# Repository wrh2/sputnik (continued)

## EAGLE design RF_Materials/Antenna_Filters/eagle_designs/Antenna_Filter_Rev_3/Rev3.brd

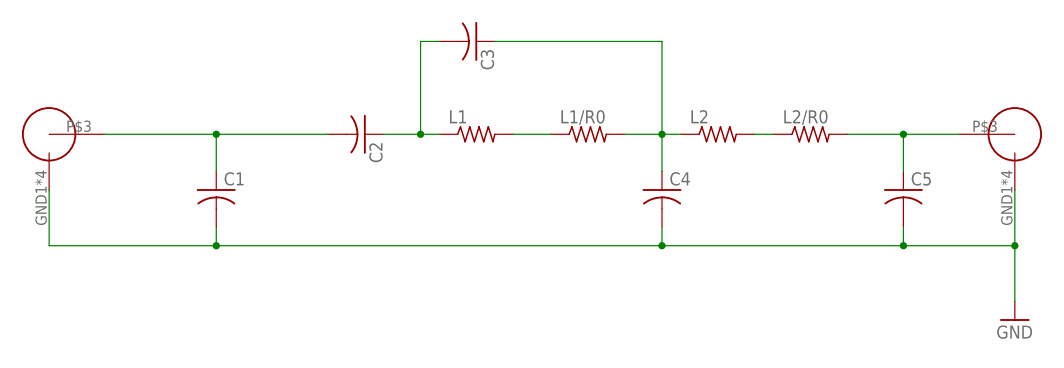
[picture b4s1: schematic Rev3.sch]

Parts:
C1, C2, C3, C4, C5: C-USC0603; C0603
L1, L1/R0, L2, L2/R0: R-US_R0603; R0603
U$1, U$2: SMAJ716-ND

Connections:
C3: C3.1, C4.1, L1/R0.2, L2.1
GND: C1.2, C4.2, C5.2, U$1.GND1 (OUTERCONDUCTOR), U$1.GND2 (OUTERCONDUCTOR), U$1.GND3 (OUTERCONDUCTOR), U$1.GND4 (OUTERCONDUCTOR), U$2.GND1 (OUTERCONDUCTOR), U$2.GND2 (OUTERCONDUCTOR), U$2.GND3 (OUTERCONDUCTOR), U$2.GND4 (OUTERCONDUCTOR)
unnamed: C5.1, L2/R0.2, U$2.P$3 (CENTERCONDUCTOR)
unnamed: L2.2, L2/R0.1
unnamed: C2.1, C3.2, L1.1
unnamed: L1.2, L1/R0.1
unnamed: C1.1, C2.2, U$1.P$3 (CENTERCONDUCTOR)

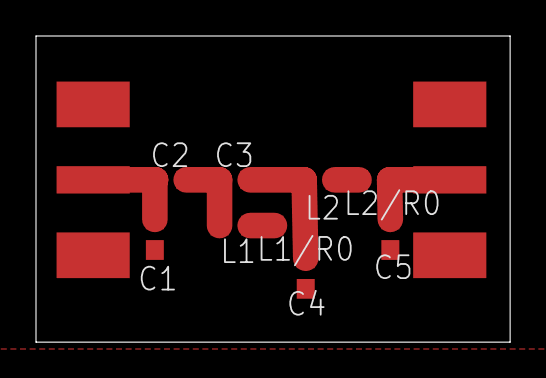
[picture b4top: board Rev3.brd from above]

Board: 2 copper layers, 26.3 x 17.0 mm, 11 parts (0 on the bottom side), 7 nets.

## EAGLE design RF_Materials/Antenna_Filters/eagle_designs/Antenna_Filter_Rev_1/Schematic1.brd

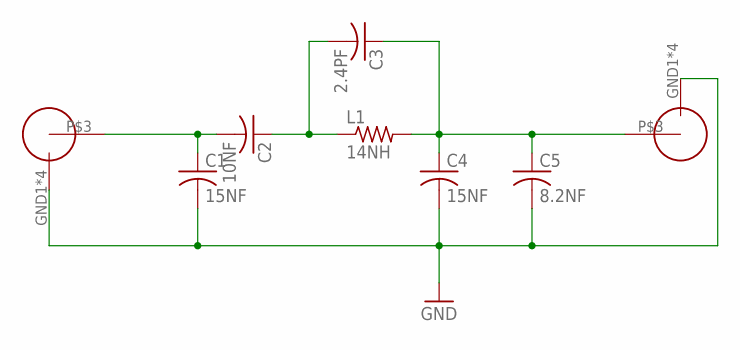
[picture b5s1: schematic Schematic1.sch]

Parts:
C1, C4: 15NF; C0603
C2: 10NF; C0603
C3: 2.4PF; C0603
C5: 8.2NF; C0603
GND: SMAJ716-ND
L1: 14NH; R0603
U$2: SMAJ716-ND

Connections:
GND: C1.2, C4.2, C5.2, GND.GND1 (OUTERCONDUCTOR), GND.GND2 (OUTERCONDUCTOR), GND.GND3 (OUTERCONDUCTOR), GND.GND4 (OUTERCONDUCTOR), U$2.GND1 (OUTERCONDUCTOR), U$2.GND2 (OUTERCONDUCTOR), U$2.GND3 (OUTERCONDUCTOR), U$2.GND4 (OUTERCONDUCTOR)
unnamed: C3.1, C4.1, C5.1, L1.2, U$2.P$3 (CENTERCONDUCTOR)
unnamed: C2.1, C3.2, L1.1
unnamed: C1.1, C2.2, GND.P$3 (CENTERCONDUCTOR)

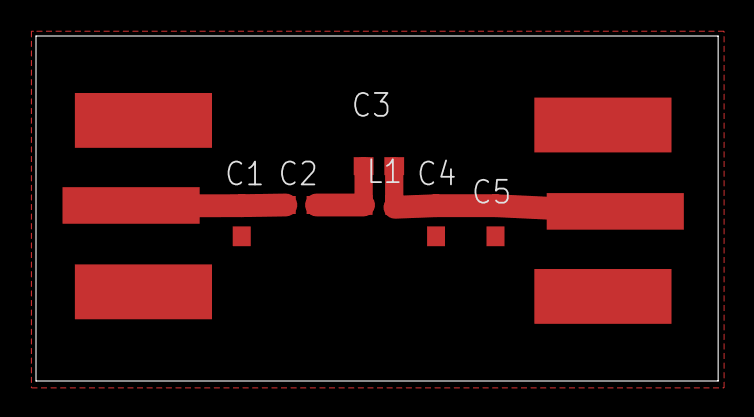
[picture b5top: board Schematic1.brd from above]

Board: 2 copper layers, 37.9 x 19.2 mm, 8 parts (0 on the bottom side), 4 nets.

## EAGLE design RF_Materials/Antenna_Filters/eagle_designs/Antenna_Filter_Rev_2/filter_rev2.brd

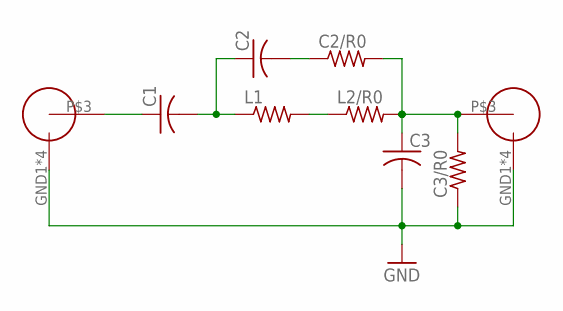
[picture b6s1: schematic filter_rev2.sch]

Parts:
C1, C2, C3: C-USC0603; C0603
C2/R0, C3/R0: R-US_R0603; R0603
L1, L2/R0: R-US_R0603; R0603
U$1, U$2: SMAJ716-ND

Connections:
GND: C3.2, C3/R0.1, U$1.GND1 (OUTERCONDUCTOR), U$1.GND2 (OUTERCONDUCTOR), U$1.GND3 (OUTERCONDUCTOR), U$1.GND4 (OUTERCONDUCTOR), U$2.GND1 (OUTERCONDUCTOR), U$2.GND2 (OUTERCONDUCTOR), U$2.GND3 (OUTERCONDUCTOR), U$2.GND4 (OUTERCONDUCTOR)
unnamed: C1.1, U$1.P$3 (CENTERCONDUCTOR)
unnamed: C2.2, C2/R0.1
unnamed: C1.2, C2.1, L1.1
unnamed: C2/R0.2, C3.1, C3/R0.2, L2/R0.2, U$2.P$3 (CENTERCONDUCTOR)
unnamed: L1.2, L2/R0.1

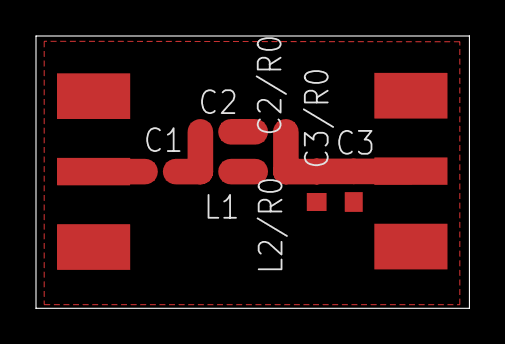
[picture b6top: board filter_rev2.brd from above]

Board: 2 copper layers, 24.1 x 15.1 mm, 9 parts (0 on the bottom side), 6 nets.

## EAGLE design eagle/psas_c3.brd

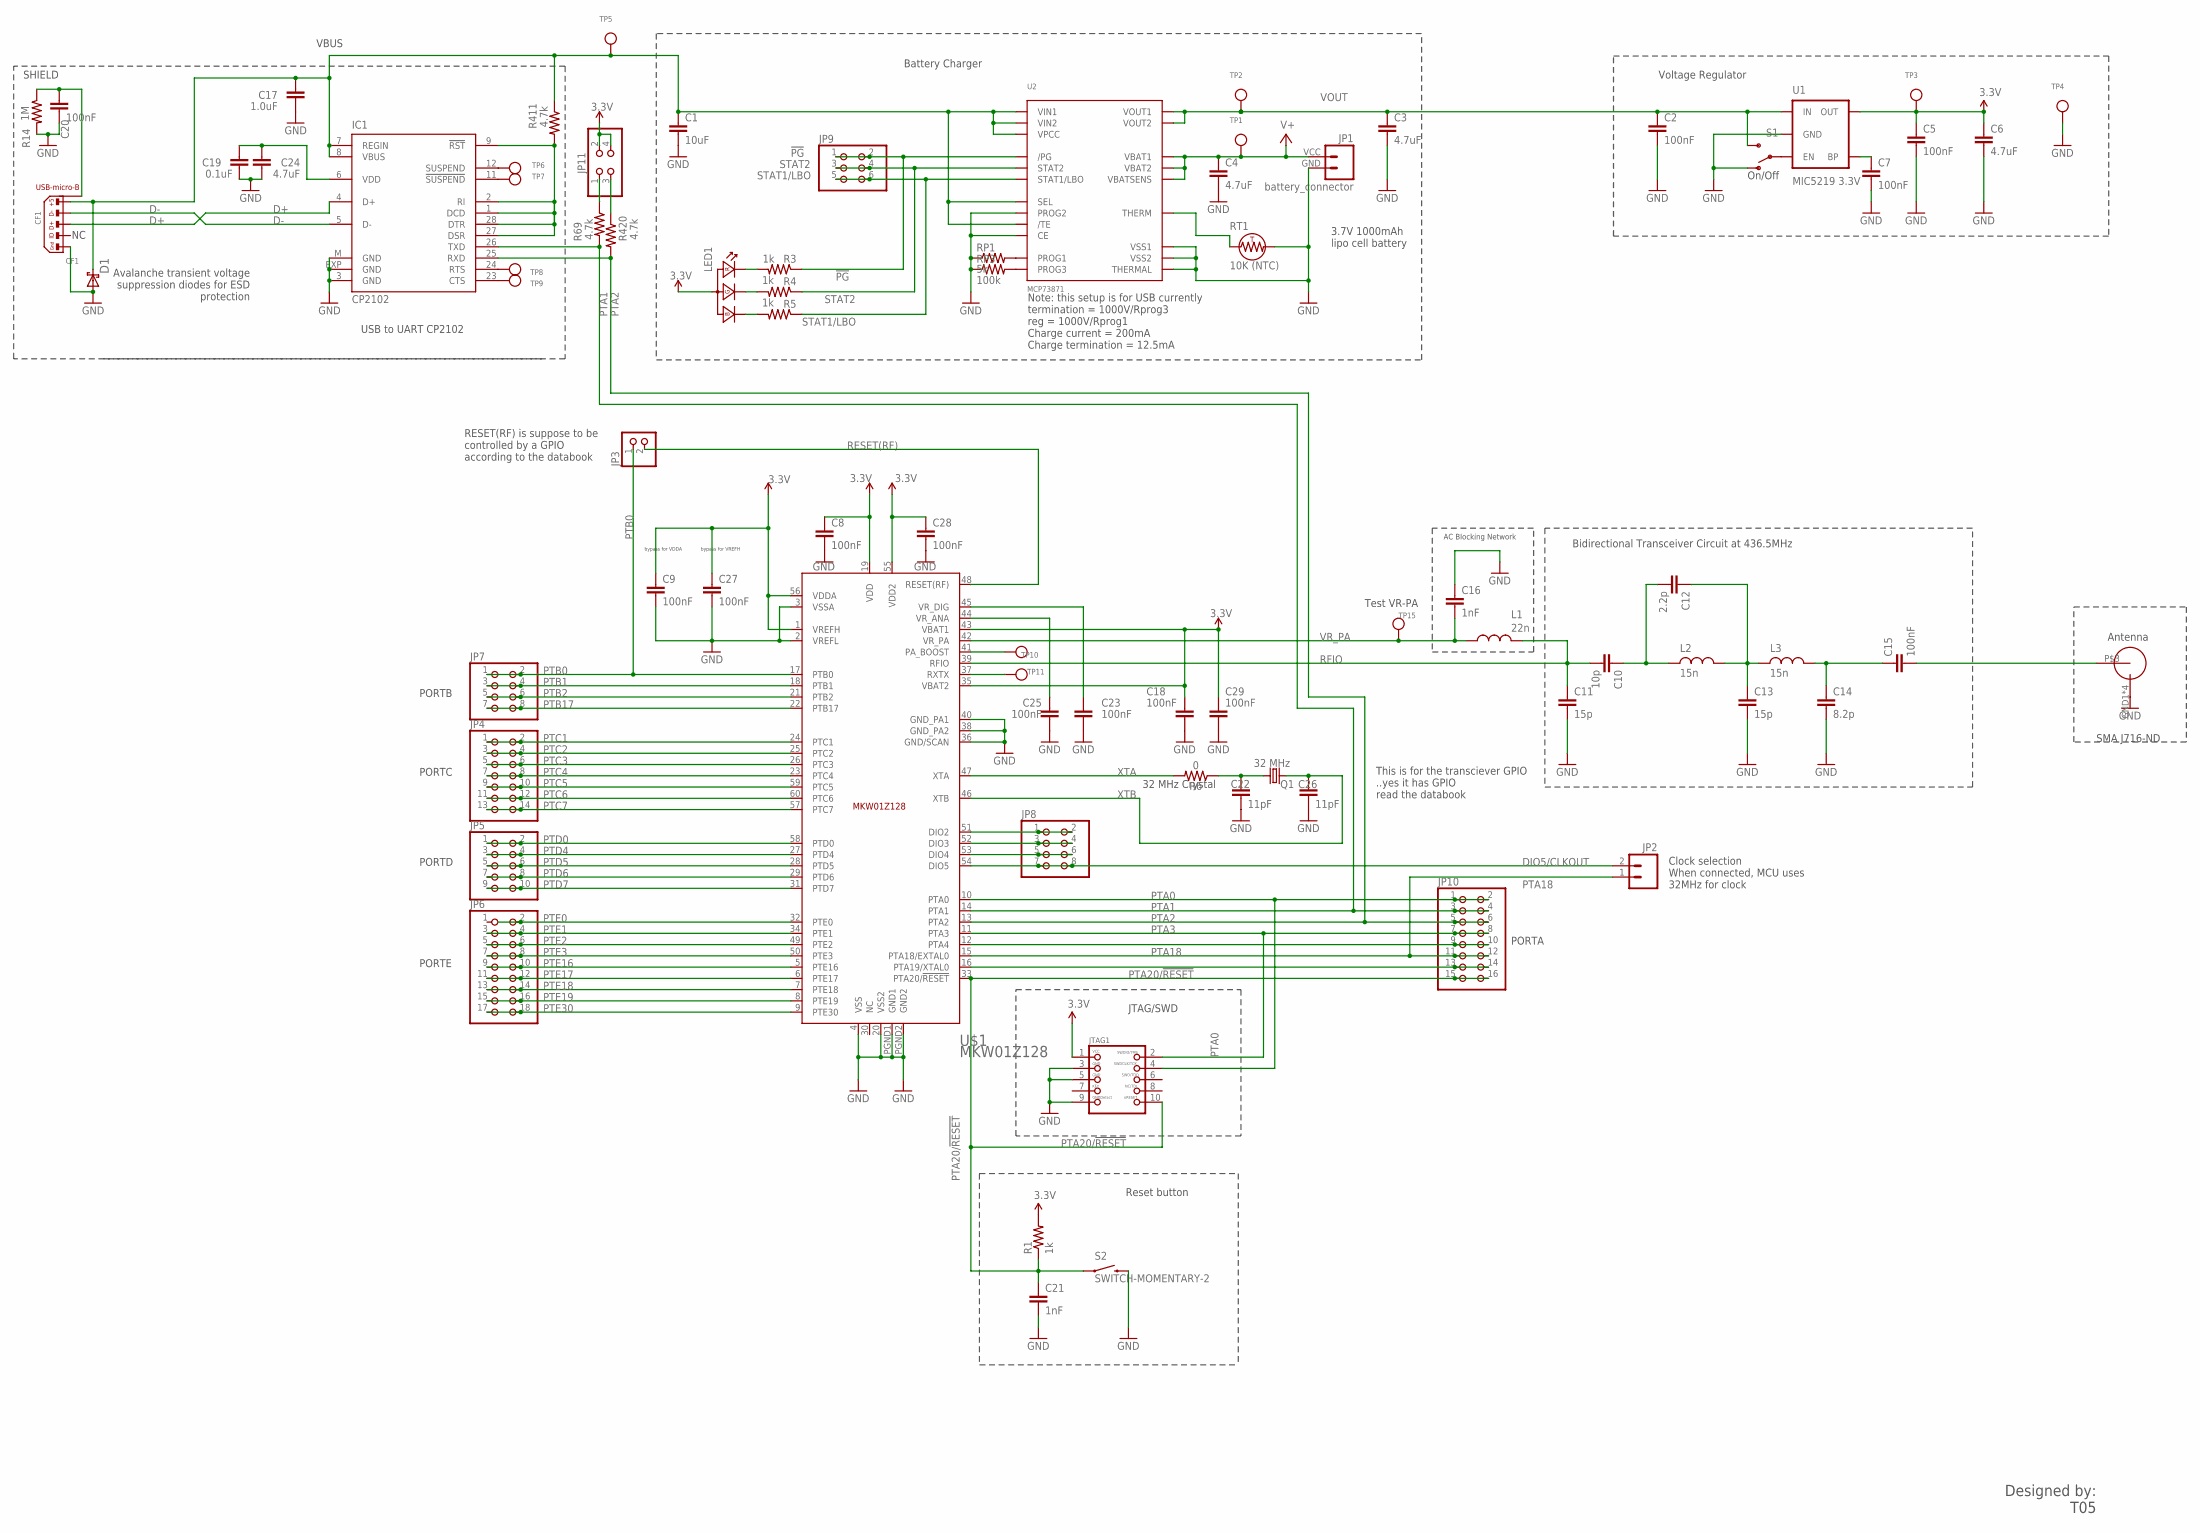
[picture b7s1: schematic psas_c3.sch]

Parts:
C1: 10uF; .0603-B-NOSILK
C2, C5, C7, C15, C20: 100nF; .0603-B-NOSILK
C3, C4, C6, C24: 4.7uF; .0603-B-NOSILK
C8, C9, C18, C23, C25, C27, C28, C29: 100nF; .0603-B-NOSILK; MPN GRM188R71C104KA01D
C10: 10p; .0603-B-NOSILK
C11, C13: 15p; .0603-B-NOSILK
C12: 2.2p; .0603-B-NOSILK
C14: 8.2p; .0603-B-NOSILK
C16, C21: 1nF; .0603-B-NOSILK
C17: 1.0uF; .0603-B-NOSILK
C19: 0.1uF; .0603-B-NOSILK
C22, C26: 11pF; .0603-B-NOSILK; MPN GRM188R71C104KA01D
CF1: CF1; USB-MICRO-B-PTH-HIROSE
D1: DIODE_SCHOTTKY_1N5819; SOD-123
IC1: CP2102; MLP28
JP1: battery_connector; SPARKFUN-CONNECTORS_JST-2-SMD-VERT
JP2: M02PTH; 1X02
JP3: PINHD-1X2; 1X02
JP4: PINHD-2X7; 2X07
JP5: PINHD-2X5; 2X05
JP6: PINHD-2X9; 2X09
JP7, JP8: PINHD-2X4; 2X04
JP9: PINHD-2X3; 2X03
JP10: PINHD-2X8; 2X08
JP11: PINHD-2X2; 2X02
JTAG1: JTAG-CORTEXM3MOLEX; CORTEXM3_SWD10_MOLEX
L1: 22n; .0603-B-NOSILK
L2, L3: 15n; .0603-B-NOSILK
LED1: LED_RGB_COMMON_ANODE-1.6X1.26; KINGBRITE_RGBLED_1.6X1.26
Q1: 32 MHz; FC-12M
R1, R3, R4, R5: 1k; .0603-B-NOSILK
R6: 0; .0603-B-NOSILK
R14: 1M; .0603-B-NOSILK
R69, R411, R420: 4.7k; .0603-B-NOSILK
RP1: 5k; .0603-B-NOSILK
RP3: 100k; .0603-B-NOSILK
RT1: 10K (NTC); R1206
S1: SWITCH-SPSTPTH; SWITCH-SPDT
S2: SWITCH-MOMENTARY-2; TACTILE_SWITCH_TALL
TP1, TP2, TP3, TP4, TP5, TP6, TP7, TP8, TP9, TP10, TP11, TP15: TESTPOINTROUND0.5MM; TESTPOINT_ROUND_0.5MM
U1: MIC5219 3.3V; SPARKFUN-POWERIC_SOT23-5
U2: MCP73871; QFN20_4MM
U$1: MKW01Z128; MPN MKW01Z128CHN
U$2: SMAJ716-ND

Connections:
3.3V: C5.1, C6.1, C8.1, C9.1, C18.1, C27.1, C28.1, C29.1, JP11.2, JP11.4, JTAG1.1, LED1.2 (COMMON_ANODE), R1.2, TP3.P$1, U1.5 (OUT), U$1.1 (VREFH), U$1.19 (VDD), U$1.35 (VBAT2), U$1.43 (VBAT1), U$1.55 (VDD2), U$1.56 (VDDA)
!PG: JP9.1, JP9.2, R3.1, U2.P$6 (/PG)
D+: CF1.3, IC1.4 (D+)
D-: CF1.2, IC1.5 (D-)
DIO5/CLKOUT: JP2.2, JP8.7, JP8.8, U$1.54 (DIO5)
GND: C1.2, C2.2, C3.2, C4.2, C5.2, C6.2, C7.2, C8.2, C9.2, C11.2, C13.2, C14.2, C16.1, C17.2, C18.2, C19.2, C20.2, C21.2, C22.2, C23.2, C24.2, C25.2, C26.2, C27.2, C28.2, C29.2, CF1.5, D1.ANODE, IC1.3 (GND), IC1.EXP (GND), IC1.M (GND), JP1.GND (1), JTAG1.3, JTAG1.5, JTAG1.9, R14.2, RP1.1, RP3.1, RT1.2, S1.1 (O), S2.B2 (2), TP4.P$1, U1.2 (GND), U2.P$4 (PROG2), U2.P$10 (VSS1), U2.P$11 (VSS2), U2.P$17 (CE), U2.P$21 (THERMAL), U$1.2 (VREFL), U$1.3 (VSSA), U$1.4 (VSS), U$1.20 (VSS2), U$1.36 (GND/SCAN), U$1.38 (GND_PA2), U$1.40 (GND_PA1), U$1.PGND1 (GND1), U$1.PGND2 (GND2), U$2.GND1 (OUTERCONDUCTOR), U$2.GND2 (OUTERCONDUCTOR), U$2.GND3 (OUTERCONDUCTOR), U$2.GND4 (OUTERCONDUCTOR)
unnamed: C7.1, U1.4 (BP)
unnamed: LED1.3 (RK), R3.2
unnamed: LED1.4 (GK), R4.2
unnamed: LED1.1 (BK), R5.2
unnamed: IC1.12 (SUSPEND), TP6.P$1
unnamed: RT1.1, U2.P$5 (THERM)
unnamed: IC1.11 (!SUSPEND), TP7.P$1
unnamed: S1.2, U1.3 (EN)
unnamed: RP1.2, U2.P$13 (PROG1)
unnamed: RP3.2, U2.P$12 (PROG3)
unnamed: IC1.24 (RTS), TP8.P$1
unnamed: C22.1, Q1.2, R6.1
unnamed: TP10.P$1, U$1.41 (PA_BOOST)
unnamed: C25.1, U$1.44 (VR_ANA)
unnamed: TP11.P$1, U$1.37 (RXTX)
unnamed: JP8.1, JP8.2, U$1.51 (DIO2)
unnamed: C12.1, C13.1, L2.2, L3.1
unnamed: C10.1, C12.2, L2.1
unnamed: C15.2, U$2.P$3 (CENTERCONDUCTOR)
unnamed: JP8.3, JP8.4, U$1.52 (DIO3)
unnamed: C14.1, C15.1, L3.2
unnamed: C23.1, U$1.45 (VR_DIG)
unnamed: JP8.5, JP8.6, U$1.53 (DIO4)
unnamed: C19.1, C24.1, IC1.6 (VDD)
unnamed: IC1.23 (CTS), TP9.P$1
unnamed: JP10.9, JP10.10, U$1.12 (PTA4)
unnamed: JP10.13, JP10.14, U$1.16 (PTA19/XTAL0)
unnamed: JP11.1, R69.1
unnamed: JP11.3, R420.1
unnamed: IC1.1 (DCD), IC1.2 (RI), IC1.9 (!RST), IC1.27 (DSR), IC1.28 (DTR), R411.2
unnamed: C20.1, CF1.S1 (SHIELD), CF1.S2 (SHIELD), CF1.S3 (SHIELD), CF1.S4 (SHIELD), R14.1
PTA0: JP10.1, JP10.2, JTAG1.4, U$1.10 (PTA0)
PTA1: IC1.26 (TXD), JP10.3, JP10.4, R69.2, U$1.14 (PTA1)
PTA2: IC1.25 (RXD), JP10.5, JP10.6, R420.2, U$1.13 (PTA2)
PTA3: JP10.7, JP10.8, JTAG1.2, U$1.11 (PTA3)
PTA18: JP2.1, JP10.11, JP10.12, U$1.15 (PTA18/EXTAL0)
PTA20/!RESET: C21.1, JP10.15, JP10.16, JTAG1.10, R1.1, S2.A2 (1), U$1.33 (PTA20/!RESET)
PTB0: JP3.1, JP7.1, JP7.2, U$1.17 (PTB0)
PTB1: JP7.3, JP7.4, U$1.18 (PTB1)
PTB2: JP7.5, JP7.6, U$1.21 (PTB2)
PTB17: JP7.7, JP7.8, U$1.22 (PTB17)
PTC1: JP4.1, JP4.2, U$1.24 (PTC1)
PTC2: JP4.3, JP4.4, U$1.25 (PTC2)
PTC3: JP4.5, JP4.6, U$1.26 (PTC3)
PTC4: JP4.7, JP4.8, U$1.23 (PTC4)
PTC5: JP4.9, JP4.10, U$1.59 (PTC5)
PTC6: JP4.11, JP4.12, U$1.60 (PTC6)
PTC7: JP4.13, JP4.14, U$1.57 (PTC7)
PTD0: JP5.1, JP5.2, U$1.58 (PTD0)
PTD4: JP5.3, JP5.4, U$1.27 (PTD4)
PTD5: JP5.5, JP5.6, U$1.28 (PTD5)
PTD6: JP5.7, JP5.8, U$1.29 (PTD6)
PTD7: JP5.9, JP5.10, U$1.31 (PTD7)
PTE0: JP6.2, U$1.32 (PTE0)
PTE1: JP6.3, JP6.4, U$1.34 (PTE1)
PTE2: JP6.5, JP6.6, U$1.49 (PTE2)
PTE3: JP6.7, JP6.8, U$1.50 (PTE3)
PTE16: JP6.9, JP6.10, U$1.5 (PTE16)
PTE17: JP6.11, JP6.12, U$1.6 (PTE17)
PTE18: JP6.13, JP6.14, U$1.7 (PTE18)
PTE19: JP6.15, JP6.16, U$1.8 (PTE19)
PTE30: JP6.17, JP6.18, U$1.9 (PTE30)
RESET(RF): JP3.2, U$1.48 (RESET(RF))
RFIO: C10.2, C11.1, L1.2, U$1.39 (RFIO)
STAT1/LBO: JP9.5, JP9.6, R5.1, U2.P$8 (STAT1/LBO)
STAT2: JP9.3, JP9.4, R4.1, U2.P$7 (STAT2)
V+: C4.1, JP1.VCC (2), TP1.P$1, U2.P$14 (VBAT1), U2.P$15 (VBAT2), U2.P$16 (VBATSENS)
VBUS: C1.1, C17.1, CF1.1, D1.CATHODE, IC1.7 (REGIN), IC1.8 (VBUS), R411.1, TP5.P$1, U2.P$2 (VPCC), U2.P$3 (SEL), U2.P$9 (/TE), U2.P$18 (VIN1), U2.P$19 (VIN2)
VOUT: C2.1, C3.1, S1.3 (S), TP2.P$1, U1.1 (IN), U2.P$1 (VOUT1), U2.P$20 (VOUT2)
VR_PA: C16.2, L1.1, TP15.P$1, U$1.42 (VR_PA)
XTA: R6.2, U$1.47 (XTA)
XTB: C26.1, Q1.1, U$1.46 (XTB)

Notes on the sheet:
Note: this setup is for USB currently termination = 1000V/Rprog3 reg = 1000V/Rprog1 Charge current = 200mA Charge termination = 12.5mA
On/Off
Voltage Regulator
Battery Charger
Designed by: T05
AC Blocking Network
Bidirectional Transceiver Circuit at 436.5MHz
USB to UART CP2102
SHIELD
VBUS
Avalanche transient voltage suppression diodes for ESD protection
JTAG/SWD
Reset button
32 MHz Crystal
3.7V 1000mAh lipo cell battery
RESET(RF) is suppose to be controlled by a GPIO according to the databook
PORTC
PORTB
PORTD
PORTE
This is for the transciever GPIO ..yes it has GPIO read the databook
Clock selection When connected, MCU uses 32MHz for clock
bypass for VDDA
bypass for VREFH
Antenna
SMA J716-ND
Test VR-PA
PORTA

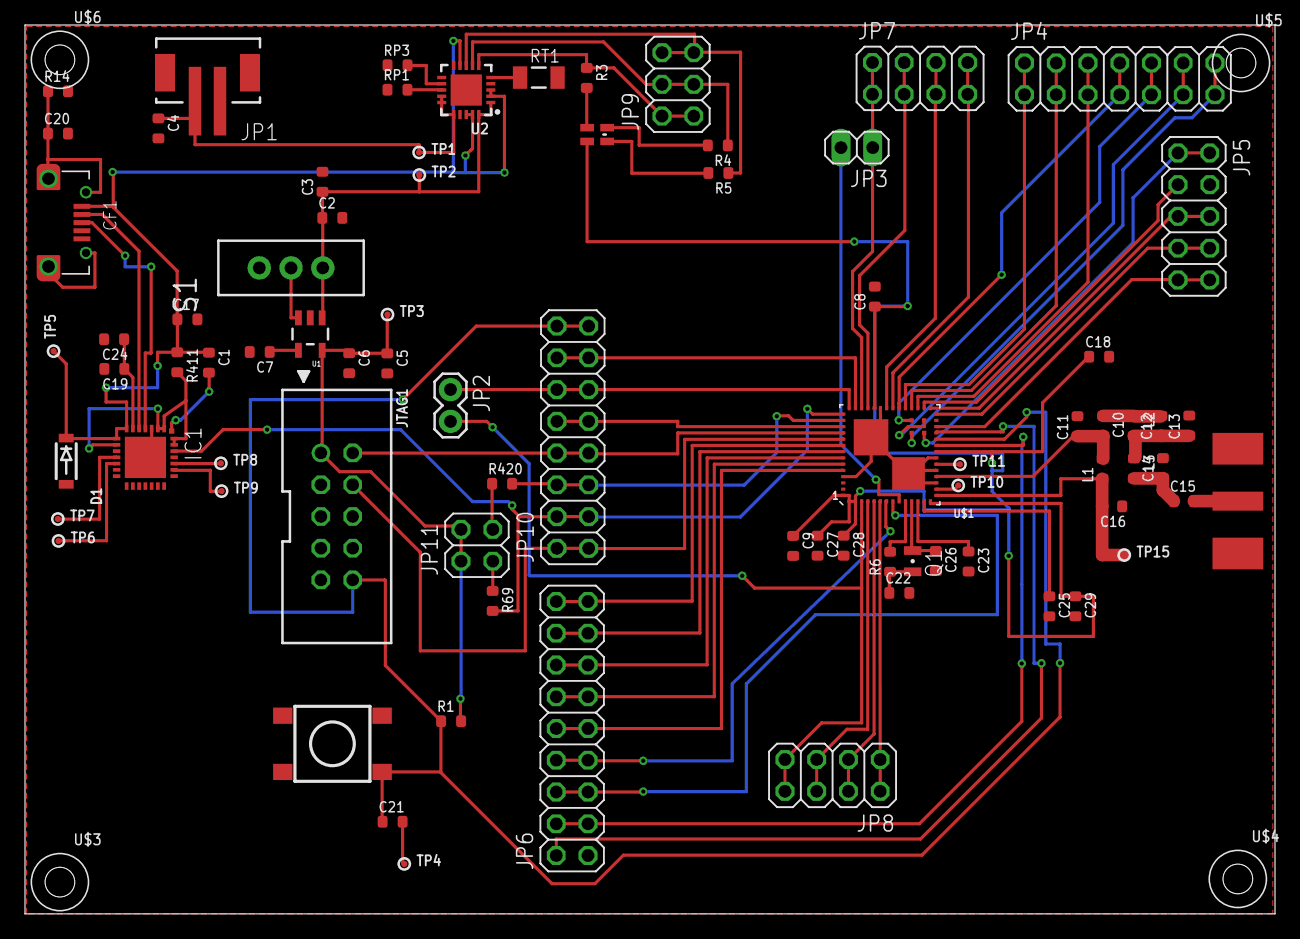
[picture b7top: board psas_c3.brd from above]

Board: 2 copper layers, 100.0 x 71.1 mm, 83 parts (0 on the bottom side), 78 nets.

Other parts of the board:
U$3, U$4, U$5, U$6: #2/.750-BARE

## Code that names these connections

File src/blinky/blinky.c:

/*
	Example code of lighting LEDs on c3 board

	Programmed by William Harrington, Michael Mathis, and Theo Hill
 */
#include "uart.h"
#include "transceiver.h"
#include "spi.h"

#if 1
void initialize_spi(void){
	/* enable clock for SPI modules */
	SIM.SCGC4 |= 0xC00000;

	/* enable clock for all ports */
	SIM.SCGC5 |= 0x3E00;

	/* The transceiver requires a specific SPI configuration*/
	initialize_trans_spi(&SPI0);

	/* Send to transceiver to get 32MHz clock signal on PTA18 */
	uint8_t RegDioMapping2Cfg = 0x0;
	trans_write_register(transceiver.RegDioMapping2, &RegDioMapping2Cfg, 1);

	/* disable SPI module clock because theo said it would get mad if I didn't! */
	SIM.SCGC4 &= 0xFF3FFFFF;

	/* disable port module clock because theo said it would get mad if I didn't! */
	SIM.SCGC5 &= 0xFFFFC1FF;

}


void initialize_clock(void){
	/* simple clock configuration that involves initializing the SPI so we can get the external clock reference from the transceiver */

	/* set PLL external reference divider (PRDIV0) to 16, this will give us 2 MHz */
	MCG.C5 = 0xF;

	/* enable MCGPLLCLK if system is in Normal Stop mode */
	MCG.C5 |= 0x40;

	/* select PLL instead of FLL */
	MCG.C6 |= 0x40;

	/* wait for PLL lock */
	while(!(MCG.S & (1 << 6)));

	/* set frequency range select to high frequency range for oscillator
	   and select external reference clock
	*/
	MCG.C2 |= 0x14;

	/* enable external oscillator */
	OSC0.CR = 0x80;

	/* now enable clock for SPI modules, AGAIN! */
	SIM.SCGC4 |= 0xC00000;

	/* enable clock for all ports */
	SIM.SCGC5 |= 0x3E00;

	/* enable clock for TPM, RTC modules */
	SIM.SCGC6 |= 0x27000000;

	return;
}
#endif
void initialize_gpio(void){
	/* procedure for getting the GPIO going on pins PTB1, PTB2, PTB17 */

	/* modify mux to select alt 1 functionality
	   for PTB1, PTB2, PTB17.
	   Alt 1 functionality is just GPIO
	*/
	PORTB.PCR[1] |= 0x100;
	PORTB.PCR[2] |= 0x100;
	PORTB.PCR[17] |= 0x100;

	/* set data direction as output */
	GPIOB.PDDR |= 0x20006;

	/* turn all LEDs of by pulling pins high */
	GPIOB.PTOR = 0x20006;

	return;
}
#if 0
void initialize_uart(void){
	/* UART0 configuration */
	struct uart_config myUART = {
		/* pin for transmit = PTA1 */
		.TX = {.port=&PORTA, .pin=1,},

		/* pin for receive = PTA2 */
		.RX = {.port=&PORTA, .pin=2,},

		/* baud rate */
		.baud = 115200,
	};
	uart0_init(&UART0, &myUART);
}

void initialize_tpm(void){
  	/* procedure for initializing Timer/PWM module */

	/* Clock mode select for each module, make TPM counter increment on every TPM counter clock */
  	TPM0.SC = 0x8;
	TPM1.SC = 0x8;
	TPM2.SC = 0x8;

	/* more needs to be done here, maybe? */
  	return;
}
#endif

int main(void) {

	/* delay loop for POR, transceiver not available for 10ms */
	for(uint32_t i = 0; i < 1000000; ++i);

	/* call initialization procedures */
	initialize_spi();
	initialize_clock();
	initialize_gpio();

	//initialize_uart();
	//initialize_tpm();
   	//asm volatile ("cpsie   i");

	/* this function is in transceiver.c if you want more details */
	//configure_transceiver_tx();

	while(1) {
		for(uint32_t i = 0; i < 1000000; ++i);

	       	/* toggle LED connected to PTB2 */
		GPIOB.PTOR = 0x00004;
	}
	return 0;
}

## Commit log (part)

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2015-11-16 fixed ground pads on MCU, generated new library that has everything in it
2015-11-16 added some attributes to parts on sch/brd
2015-11-17 Added part numbers for the voltage regulator and usb to uart
2015-11-18 added a bunch of part numbers
2015-11-18 Added hw 05 part 1
2015-11-18 Final Draft of HW #5
2015-11-18 HW5 posted
2015-11-18 Added final version of HW_05
2015-11-18 Modified part attributes for RF
2015-11-18 Removed Antenna Filter folder
2015-11-18 Added final part attrib RF
2015-11-18 added attributes to battery connector, tri color LEDS
2015-11-21 Fixed changed components on the layout
2015-11-21 Made some changes to requirements
2015-11-23 Cleaned up the stencil, the usb to uart footprint was bad
2015-11-24 Updated the schedule. Still not perfect, but we will review on wednesday, 11/25
2015-11-24 Added test cases. Work in Progress
2015-11-25 Finished test conditions
2015-11-25 Got rid of appendix
2015-11-27 deleted Filter and Amplifier duplicates
2015-11-28 revision of readme
2015-11-30 took extra crystal off schematic, corrected bogus airwire
2015-12-02 started issues text file, these should be replicated on the repo
2015-12-02 Added GPIO, OSC, and SIM register blocks
2015-12-04 Defined MCG section in kw0x.h
2015-12-04 Added firmware GDB make target
    To start gdb debugging on the firmware issue `make gdb`.
    This will start GDB, start openocd inside of itself, and then halt
    the chip.
    Also a minor cleanup of the makefile
2015-12-04 Initial algorithm to use external oscillator
2015-12-05 Added more on the presentation
2015-12-05 added SPI block to header file, tried to make functions for initialization procedures but they don't work I guess, also made different snippets of example code for reference
2015-12-07 Added freescale's drivers, linkers, etc. There are more files in that exe, but I think these are the most relevant
2015-12-08 Final Clock config
2015-12-08 Added the freescale api docs
2015-12-09 Modification in HW5
2015-12-09 Made a change to RF testing slide
2015-12-10 Changed some Final Presentation Stuff
2015-12-10 Revert "Final Project changes"
    This reverts commit d92d7db23d964a298613bc6a2529ed2bf12aaeac.
2015-12-10 Latest version of the presentation 12/9
2015-12-10 New pdf for HW5
2015-12-10 updated the level 1, level 0, and additional tools
2015-12-10 Filled out the Passed sections on the GPIO test and on the JTAG to MCU
2015-12-10 I don't remember making changes. Git told me to do this.
2015-12-10 Our final version of the presentation
2015-12-15 Another makefile mod
    changed -nostdlib to -nostarterfiles, needed to do this so I could do things like use arrays...
2015-12-15 Transceiver register mapping
    Just saving my progress.
2015-12-16 First version of SPI Module 0 driver
2015-12-16 Added comments to SPI revision
    It needed comments badly. Commented all that black magic juju.
2015-12-18 Added static unit tests for register definitions
    Using C11's new _Static_assert() means we can have compile time checks
    for getting the register definitions correct. In this instance I take
    the last register of each module and compare it to the value in the
    Reference manual.
    In this way we can verify that the combination of register sizes and
    padding is correct up to the last register. It does *not* catch
2015-12-18 Resolving the merge
    Reintroduced code I had done prior that got scrapped during merge
2015-12-21 Added dual ouput design sim
2015-12-25 First version of generalized SPI driver
2015-12-26 corrected error in init function
2016-01-06 got rid of test file
2016-01-08 Openocd program command takes exit as an argument
2016-01-08 CHECK_DEFINITION verifies that the given reg is the last one
    This should prevent junk fields from being added to the end of perpheral
    struct definitions
2016-01-08 continued adding r/w, read-only, and write-only annotations
2016-01-10 Added static checks for DMA 0-2
2016-01-11 Added flash configuration section, removed excess stacks
2016-01-11 Set standard to C11
    It's the future, we can use cool things like C11
2016-01-11 updated readme with link to wiki article on explanation
2016-01-13 Change spi driver to pass peripheral by pointer
    Passing by value means the struct gets copied to an arbitrary location
    in memory - any modifications won't change the actual memory mapped
    peripheral.
2016-01-13 Grouped peripheral instances and sorted by chapter
    In doing so I found the FTFA module was missing.
2016-01-13 Rename peripheral structs
    The _t postfix is reserved by libc, it should not be used for user
    defined types.
2016-01-13 Added RW annotations to the cmp and dac modules
2016-01-13 Fixed compile errors in spi driver
    Oh how I wish C would do what I meant instead of what I wrote. Having to
    add & pretty much everywhere is kind of lame and remembering to write
    volatile struct * peripheral will probably get tiring soon. I may
    re-think the declaration scheme I had going in the near future, but not
    until I try the full static config first.
2016-01-14 finished SPI driver implementation, used in c3.c to get the 32MHz signal from the transceiver to the MCU
2016-01-15 Added a link to the google sheet schedule. Setting it to be viewable by anywone, but editable only by us
2016-01-24 cleaned up the organization a little bit
2016-01-27 added datasheets for mcu and system controller
2016-01-30 Code for transmitting carrier frequency
    Made changes to c3.c to make KW0x send carrier frequency.
    Added helper function to spi driver for masking bytes for transactions.
2016-02-01 filter photos
2016-02-08 Adding some documentation
2016-02-08 WIP transceiver driver header. Needs to have inputs and outputs double checked.
2016-02-10 initial uart driver, don't look its bad right now
2016-02-10 RF schematic update. Finished PA footprint
2016-02-10 7/28 Functions written
2016-02-11 Added datasheets for RF network parts
2016-02-13 Drivers progress
    Created separate driver for port modules. Continued working on UART driver. Made some changes to SPI driver. Had to comment out some code in c3.c and not compile with transceiver stuff because its st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
2016-02-14 Transceiver driver included in make
    Commented out a lot of code under development in transceiver driver so code would compile. Had to put in "include guards". Also had to make change transceiver declaration to extern so it only gets cr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
2016-02-14 datasheet for xtal on kw0x
2016-02-14 trying to remove redundant files
2016-02-14 POR reset bug
    MCU wasn't behaving as expected after Power-on reset. This was due to the fact that the transceiver is unavailable for 10ms after a POR. I added a delay loop in the beginning of main to resolve the i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
2016-02-17 System controller firmware
    Started simple makefile and made a basic program. Compiled and tested.
2016-02-17 Missed some declarations
2016-02-21 Added AIAA directory and proposal
2016-02-23 Lowlevel diagram
2016-02-24 Updated the schematic a bit. Removed I2C line to payload and sense pin
2016-02-25 Added very little
2016-02-26 Prototype new 8/16 bit generic spi interface
2016-02-27 Added some FSK packet test broadcasting
2016-02-27 Removed mask_spi_addr
    This is no longer needed because we're doing 8 bit mode
2016-02-27 trying to track down spi bug, compiles right now but not behaving as it should be
2016-02-27 Removed AIAA since it doesn't even have the right document anyway
2016-02-28 Added GPIOs and other updates on SysCon sch. Updated SPI cache footprint
2016-02-28 Added LNA LDO footprint and circuitry
2016-02-29 Fixed to do list
2016-02-29 Added power management parts
2016-03-01 switched memcopy to manual for loop
2016-03-02 hooked up SPI cache
2016-03-03 Added optocoupler datasheet and into the schematic
2016-03-03 added attributes to several parts, started organizing the board to prep for layout
2016-03-03 removed some test files that are no longer needed:
2016-03-04 threw configure_transceiver back into c3, seems to be working, fixed transceiver driver bugs
2016-03-04 Tets Plan is added for review
2016-03-04 got configure_transceiver function to transmit again
2016-03-05 revised source for requirements to match with whats on wiki
2016-03-05 Had to fix to do again because I'm a dumbass
2016-03-06 decided 2nd harm vs output power is something we care about more
2016-03-09 added notes
2016-03-18 fixed symbols
2016-03-19 Added the diodes and fixed the Crystal
2016-03-19 Lots of OCD cleanup on schematic, bringing up to PSAS standards. Fixed lack of bypass cap on SPI flash, changed SPI flash KW0x pins to SPI1 which weren't before (?), removed DIO1 and DIO0 from GPIO b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
2016-03-21 Fixed 22x2pinout, added PWR LEDs, fixed some NC issues
2016-03-22 Added RESET (RF) line to PTE2 GPIO. Waiting on LNA component values from MAACOM.
2016-03-23 Added crystal test point, started layout setup
2016-03-23 Clean up on system controller board. Added 40 pin connector, board outline, ground planes. Killed all old spurious signals. Removed unecessary connectors. Still need to find small power controllers t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
2016-03-24 Not much, just did some more positioning
2016-03-25 Attached SPI cache
2016-03-26 Attached bypass caps, made some connections between LDO and SPI cache components
2016-03-29 Added a spi_init_8 for 8 bit specific initialization. This includes SPIMODE = 0 and setting up PTD0 as a GPIO instead of automatically controlled by the SPI module.
    In spi.c I changed the spi_transaction_8 so that the first byte read is ignored and an arbitrary read command is sent to the transceiver to get the last valid byte out of the transceiver's shift regi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
    These changes need to be tested.
2016-03-30 Fixed symbol pins and locations
2016-03-31 All that's remaining is one annoying airwire and test points
2016-03-31 Same as our usual test, but everything is done in 8 bit mode.
2016-04-01 added the footprint for the switch
2016-04-01 Added the bare switch and deleted some text
2016-04-01 Added some review text from Glenn for changing later
2016-04-02 Started converting to RF_GND, routed a line for Jake.
2016-04-02 Moved power plane from under the RF portion of the board. Changed RF trace width to calculated 0.343mm.
2016-04-02 Finished placing test points, finished all unrouted airwires, got rid of all drill clearance errors. There are DRC errors of some of the polygons and other areas I'm not sure about.
2016-04-03 A few more changes
2016-04-04 added the 16:1 mux to the library
2016-04-04 minor changes on the mux
2016-04-05 memset and memcpy not working, replaced with for loops
2016-04-14 Trying to fix a dumbass mistake
2016-04-15 Proposed this change for how firmware experiments are organized. Each experiment has an individual directory. Created top level Makefile example for building all experiments. Added some .gitignores a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
2016-04-18 Update Test_Plan_Sputnik_Capstone.md
    Added all tests we're asked to perform. Added Supply Range Test grid and Temperature Test Grid.
2016-04-18 Update Test_Plan_Sputnik_Capstone.md
    Added grids for all component tests
2016-04-18 Update Parts_Selection.md
    Added all parts (I believe) and some notes on each part.
2016-04-20 Update Parts_Selection.md
    Minor link changes
2016-04-20 Update Test_Plan_Sputnik_Capstone.md
    Fixed ToC error and updated Revision History
2016-05-17 Removed an old version of the poster
2016-05-20 minor tweak
2016-05-25 Almost final version
2016-05-25 Small formatting and adding some content
2016-06-09 Added to Future additions, things we learned, and impact
2016-06-09 Update Test_Plan_Sputnik_Capstone.md
    Added all tests that were updated in the wiki
